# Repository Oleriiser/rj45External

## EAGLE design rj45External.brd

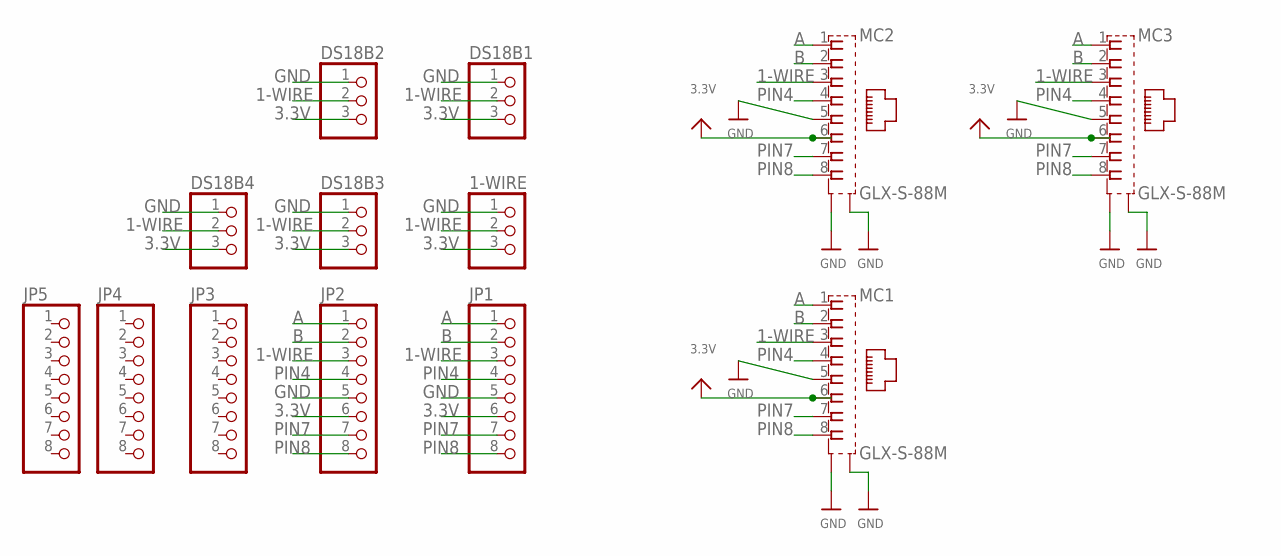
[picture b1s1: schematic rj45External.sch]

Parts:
1-WIRE: PINHD-1X3; 1X03
DS18B1, DS18B2, DS18B3, DS18B4: PINHD-1X3; 1X03
JP1, JP2, JP3, JP4, JP5: PINHD-1X8BIG; 1X08-BIG
MC1, MC2, MC3: GLX-S-88M

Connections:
1-WIRE: 1-WIRE.2, DS18B1.2, DS18B2.2, DS18B3.2, DS18B4.2, JP1.3, JP2.3, MC1.3, MC2.3, MC3.3
3.3V: 1-WIRE.3, DS18B1.3, DS18B2.3, DS18B3.3, DS18B4.3, JP1.6, JP2.6, MC1.6, MC2.6, MC3.6
A: JP1.1, JP2.1, MC1.1, MC2.1, MC3.1
B: JP1.2, JP2.2, MC1.2, MC2.2, MC3.2
GND: 1-WIRE.1, DS18B1.1, DS18B2.1, DS18B3.1, DS18B4.1, JP1.5, JP2.5, MC1.5, MC1.S1, MC1.S2, MC2.5, MC2.S1, MC2.S2, MC3.5, MC3.S1, MC3.S2
PIN4: JP1.4, JP2.4, MC1.4, MC2.4, MC3.4
PIN7: JP1.7, JP2.7, MC1.7, MC2.7, MC3.7
PIN8: JP1.8, JP2.8, MC1.8, MC2.8, MC3.8

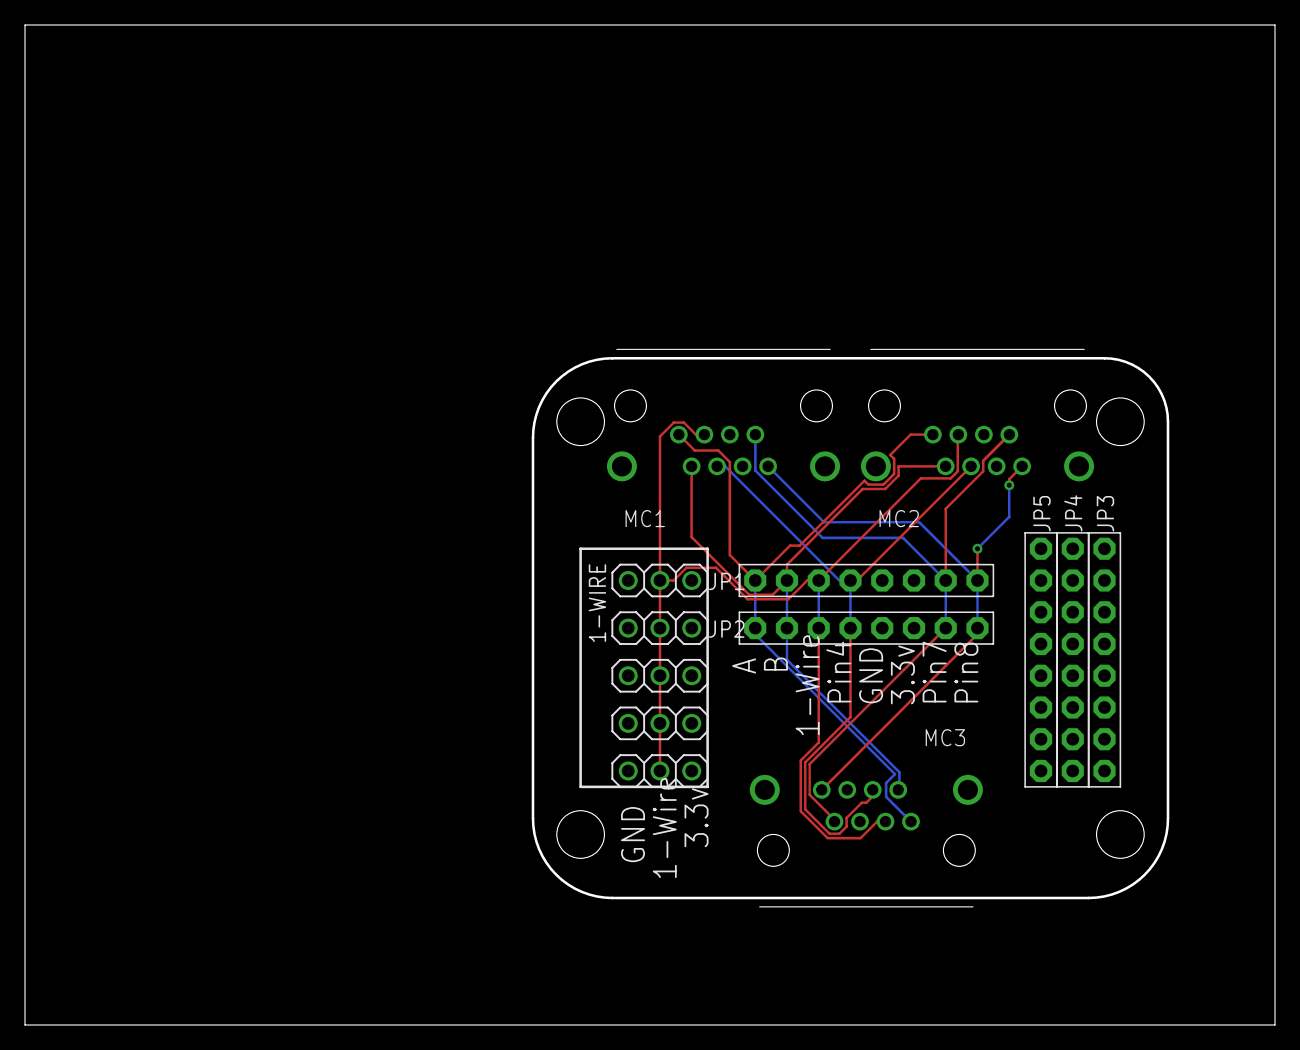
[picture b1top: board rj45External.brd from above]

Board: 2 copper layers, 100.0 x 80.0 mm, 13 parts (0 on the bottom side), 8 nets.

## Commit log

2020-04-07 added gerber
2020-04-07 added board image
2020-04-08 made enclosure
    added 2 enclosures w. Lid

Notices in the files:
parts and their libraries:
microbuilder: This work is placed in the public domain, and may be freely used for commercial and non-commercial work with the following conditions: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
